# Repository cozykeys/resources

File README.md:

# CozyKeys Resources

- [./assets](./assets): Various assets used on CozyKeys website, keyboards, etc.
- [./concepts](./concepts): Unfinished keyboard concepts
- [./cozy-components](./cozy-components): Kicad symbol library
- [./cozy-parts.pretty](./cozy-parts.pretty): Kicad footprint library
- [./guides](./guides): Guides related to keyboard creation
- [./kbutil](./kbutil): .NET Core tools for accelerating keyboard creation
- [./scripts](./scripts): Various scripts related to keyboard creation

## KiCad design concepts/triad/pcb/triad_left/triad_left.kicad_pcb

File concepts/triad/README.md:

# CozyKeys Triad

TODO

## Using the Scripts

### Install Prerequisites

```bash
python3 -m pip install \
    mypy \
    sympy \
    openpyscad
```

### General Usage

```
./scripts/triad.py <command> <ARGUMENTS> [OPTIONS]
```

## Random Resources

- XML beautifier used to format layout files:
    - [XML Beautifier](https://xmlbeautifier.com)
- Script for scaling Kicad modules, useful for graphics:
    - [Kicad Module Scaler](http://www.smallbulb.net/kicad_mod-scaler)

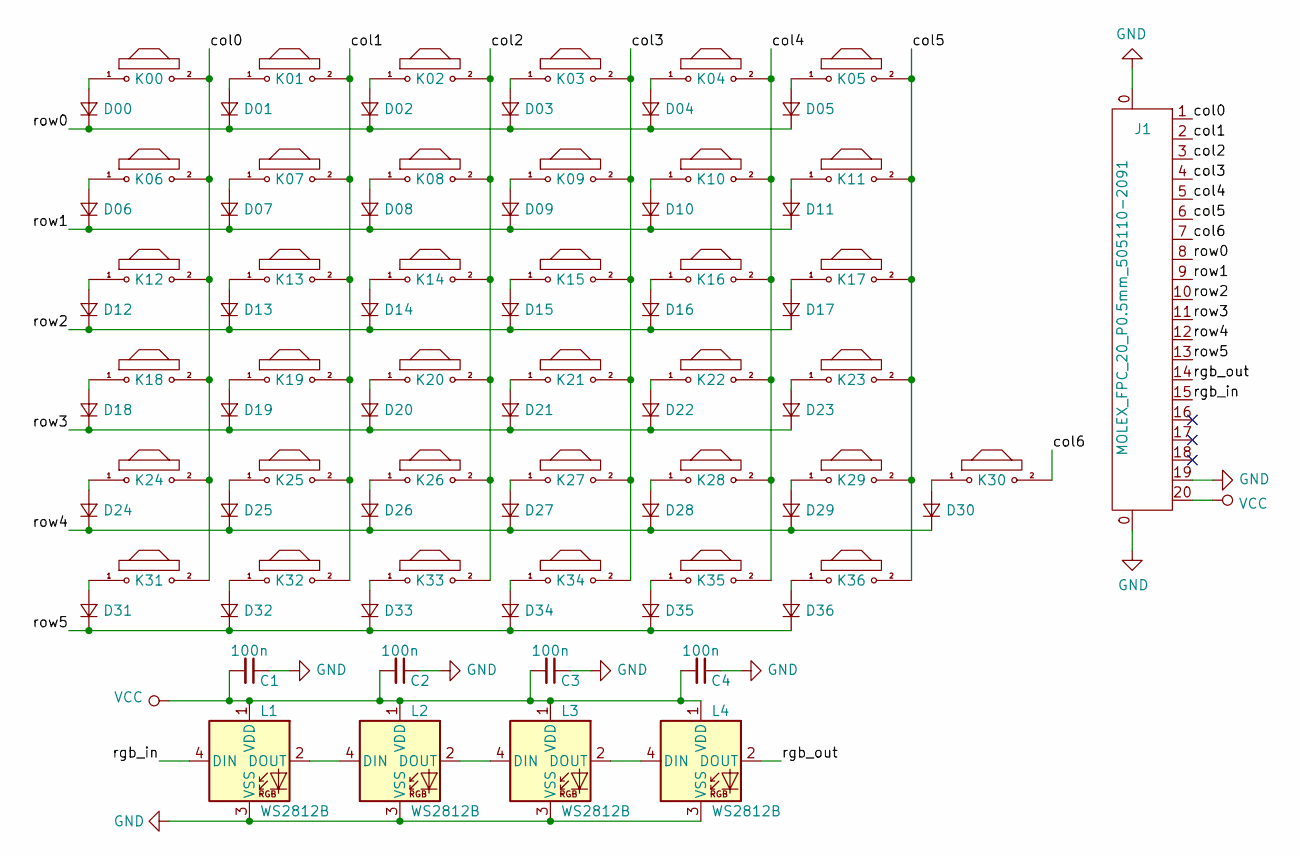
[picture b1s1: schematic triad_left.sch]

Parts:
C1, C2, C3, C4: 100n; C_0805_2012Metric_Pad1.15x1.40mm_HandSolder
D00, D01, D02, D03, D04, D05, D06, D07, D08, D09, D10, D11, D12, D13, D14, D15, D16, D17, D18, D19, D20, D21, D22, D23, D24, D25, D26, D27, D28, D29, D30, D31, D32, D33, D34, D35, D36: D_Small; D_SOD-123F
J1: MOLEX_FPC_20_P0.5mm_505110-2091
K00, K01, K02, K03, K04, K05, K06, K07, K08, K09, K10, K11, K12, K13, K14, K15, K16, K17, K18, K19, K20, K21, K22, K23, K24, K25, K26, K27, K28, K29, K30, K31, K32, K33, K34, K35, K36: MX; MX_1.00u
L1, L2, L3, L4: WS2812B; LED_WS2812B_PLCC4_5.0x5.0mm_P3.2mm

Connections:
/col0: J1.1, K00.2, K06.2, K12.2, K18.2, K24.2, K31.2
/col1: J1.2, K01.2, K07.2, K13.2, K19.2, K25.2, K32.2
/col2: J1.3, K02.2, K08.2, K14.2, K20.2, K26.2, K33.2
/col3: J1.4, K03.2, K09.2, K15.2, K21.2, K27.2, K34.2
/col4: J1.5, K04.2, K10.2, K16.2, K22.2, K28.2, K35.2
/col5: J1.6, K05.2, K11.2, K17.2, K23.2, K29.2, K36.2
/col6: J1.7, K30.2
/rgb_in: J1.15, L1.4 (DIN)
/rgb_out: J1.14, L4.2 (DOUT)
/row0: D00.1 (K), D01.1 (K), D02.1 (K), D03.1 (K), D04.1 (K), D05.1 (K), J1.8
/row1: D06.1 (K), D07.1 (K), D08.1 (K), D09.1 (K), D10.1 (K), D11.1 (K), J1.9
/row2: D12.1 (K), D13.1 (K), D14.1 (K), D15.1 (K), D16.1 (K), D17.1 (K), J1.10
/row3: D18.1 (K), D19.1 (K), D20.1 (K), D21.1 (K), D22.1 (K), D23.1 (K), J1.11
/row4: D24.1 (K), D25.1 (K), D26.1 (K), D27.1 (K), D28.1 (K), D29.1 (K), D30.1 (K), J1.12
/row5: D31.1 (K), D32.1 (K), D33.1 (K), D34.1 (K), D35.1 (K), D36.1 (K), J1.13
GND: C1.1, C2.1, C3.1, C4.1, J1.0, J1.19, L1.3 (VSS), L2.3 (VSS), L3.3 (VSS), L4.3 (VSS)
unnamed: D00.2 (A), K00.1
unnamed: D01.2 (A), K01.1
unnamed: D02.2 (A), K02.1
unnamed: D03.2 (A), K03.1
unnamed: D04.2 (A), K04.1
unnamed: D05.2 (A), K05.1
unnamed: D06.2 (A), K06.1
unnamed: D07.2 (A), K07.1
unnamed: D08.2 (A), K08.1
unnamed: D09.2 (A), K09.1
unnamed: D10.2 (A), K10.1
unnamed: D11.2 (A), K11.1
unnamed: D12.2 (A), K12.1
unnamed: D13.2 (A), K13.1
unnamed: D14.2 (A), K14.1
unnamed: D15.2 (A), K15.1
unnamed: D16.2 (A), K16.1
unnamed: D17.2 (A), K17.1
unnamed: D18.2 (A), K18.1
unnamed: D19.2 (A), K19.1
unnamed: D20.2 (A), K20.1
unnamed: D21.2 (A), K21.1
unnamed: D22.2 (A), K22.1
unnamed: D23.2 (A), K23.1
unnamed: D24.2 (A), K24.1
unnamed: D25.2 (A), K25.1
unnamed: D26.2 (A), K26.1
unnamed: D27.2 (A), K27.1
unnamed: D28.2 (A), K28.1
unnamed: D29.2 (A), K29.1
unnamed: D30.2 (A), K30.1
unnamed: D31.2 (A), K31.1
unnamed: D32.2 (A), K32.1
unnamed: D33.2 (A), K33.1
unnamed: D34.2 (A), K34.1
unnamed: D35.2 (A), K35.1
unnamed: D36.2 (A), K36.1
unnamed: L1.2 (DOUT), L2.4 (DIN)
unnamed: L2.2 (DOUT), L3.4 (DIN)
unnamed: L3.2 (DOUT), L4.4 (DIN)
VCC: C1.2, C2.2, C3.2, C4.2, J1.20, L1.1 (VDD), L2.1 (VDD), L3.1 (VDD), L4.1 (VDD)

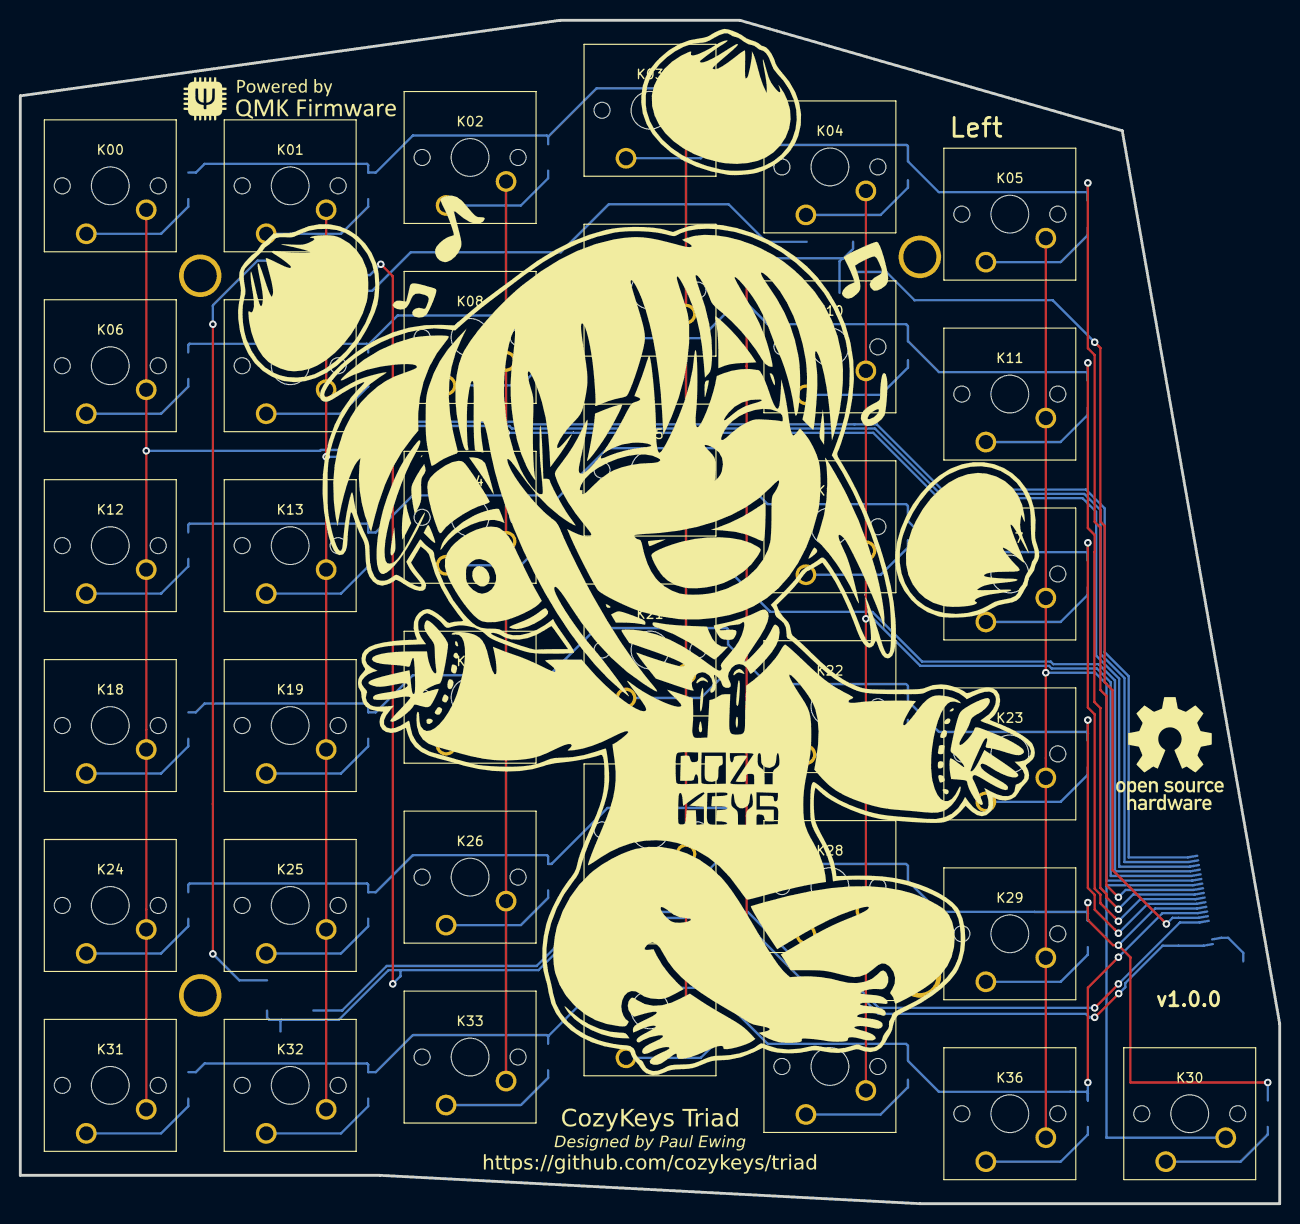
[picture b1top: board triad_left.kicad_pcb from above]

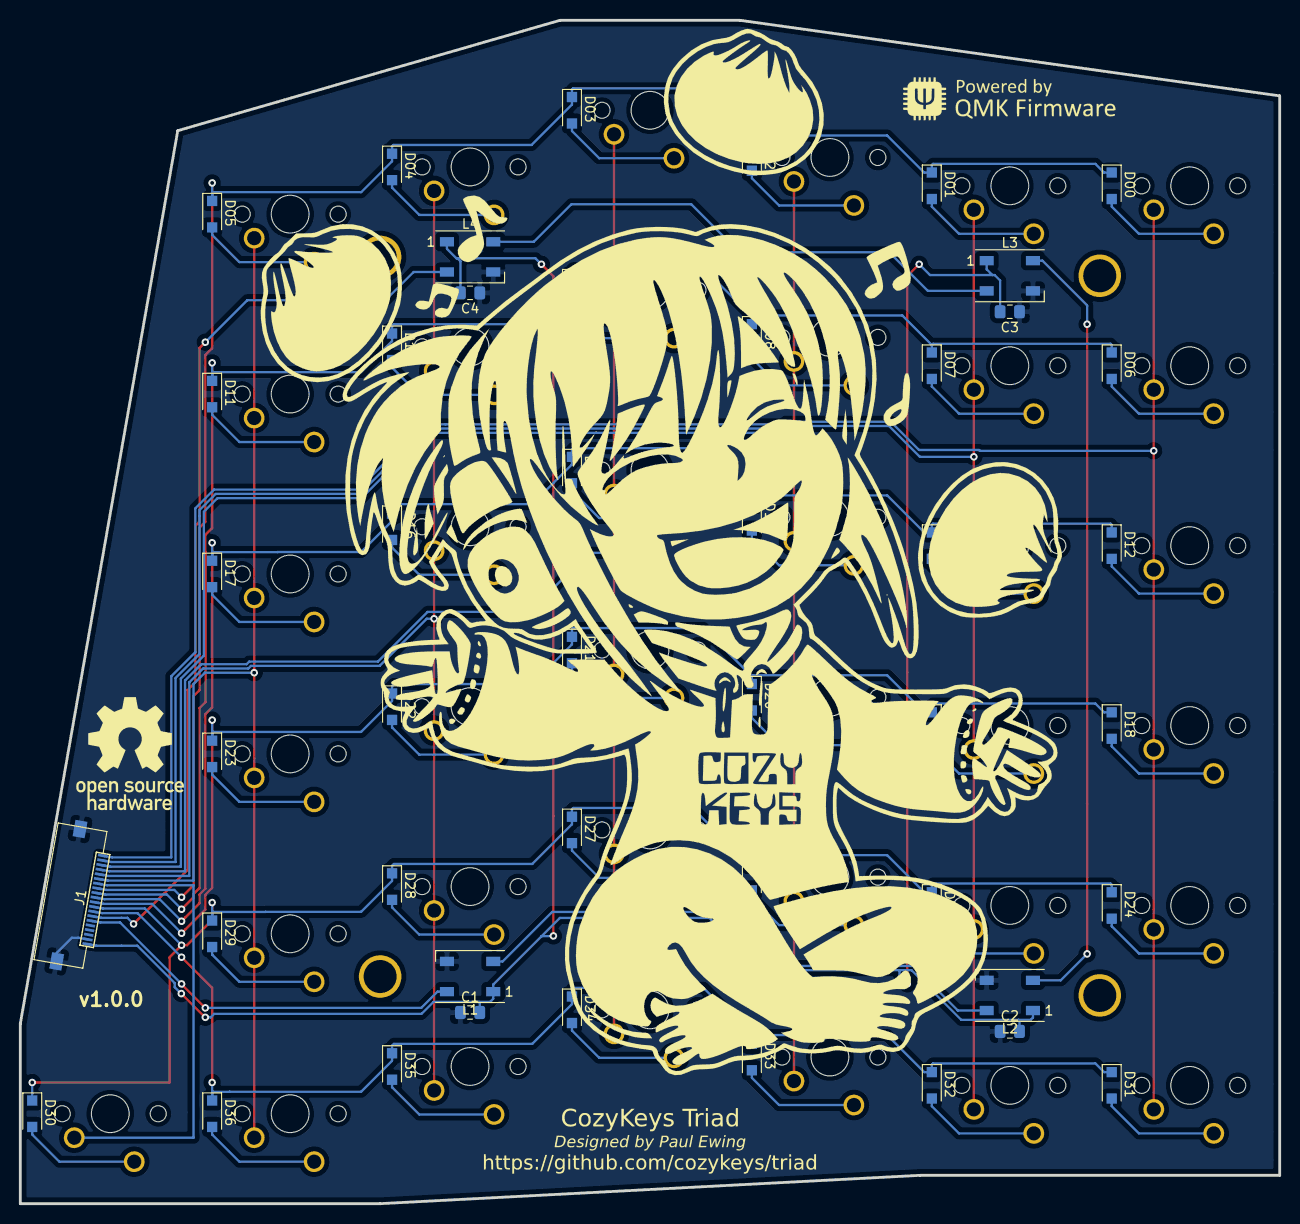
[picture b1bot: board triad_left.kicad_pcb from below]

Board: 2 copper layers, 133.3 x 125.3 mm, 93 parts (46 on the bottom side), 57 nets.

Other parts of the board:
G1, G2: LOGO; oshw-logo-small
G3, G4: qmk-badge
G5, G6: LOGO; triad-attribution-small
H1, H2, H3, H4: VAL**; HOLE_M2_SPACER

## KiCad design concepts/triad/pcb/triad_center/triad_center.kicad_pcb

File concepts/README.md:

# CozyKeys Concepts

This directory contains various concepts and unfinished keyboard designs.

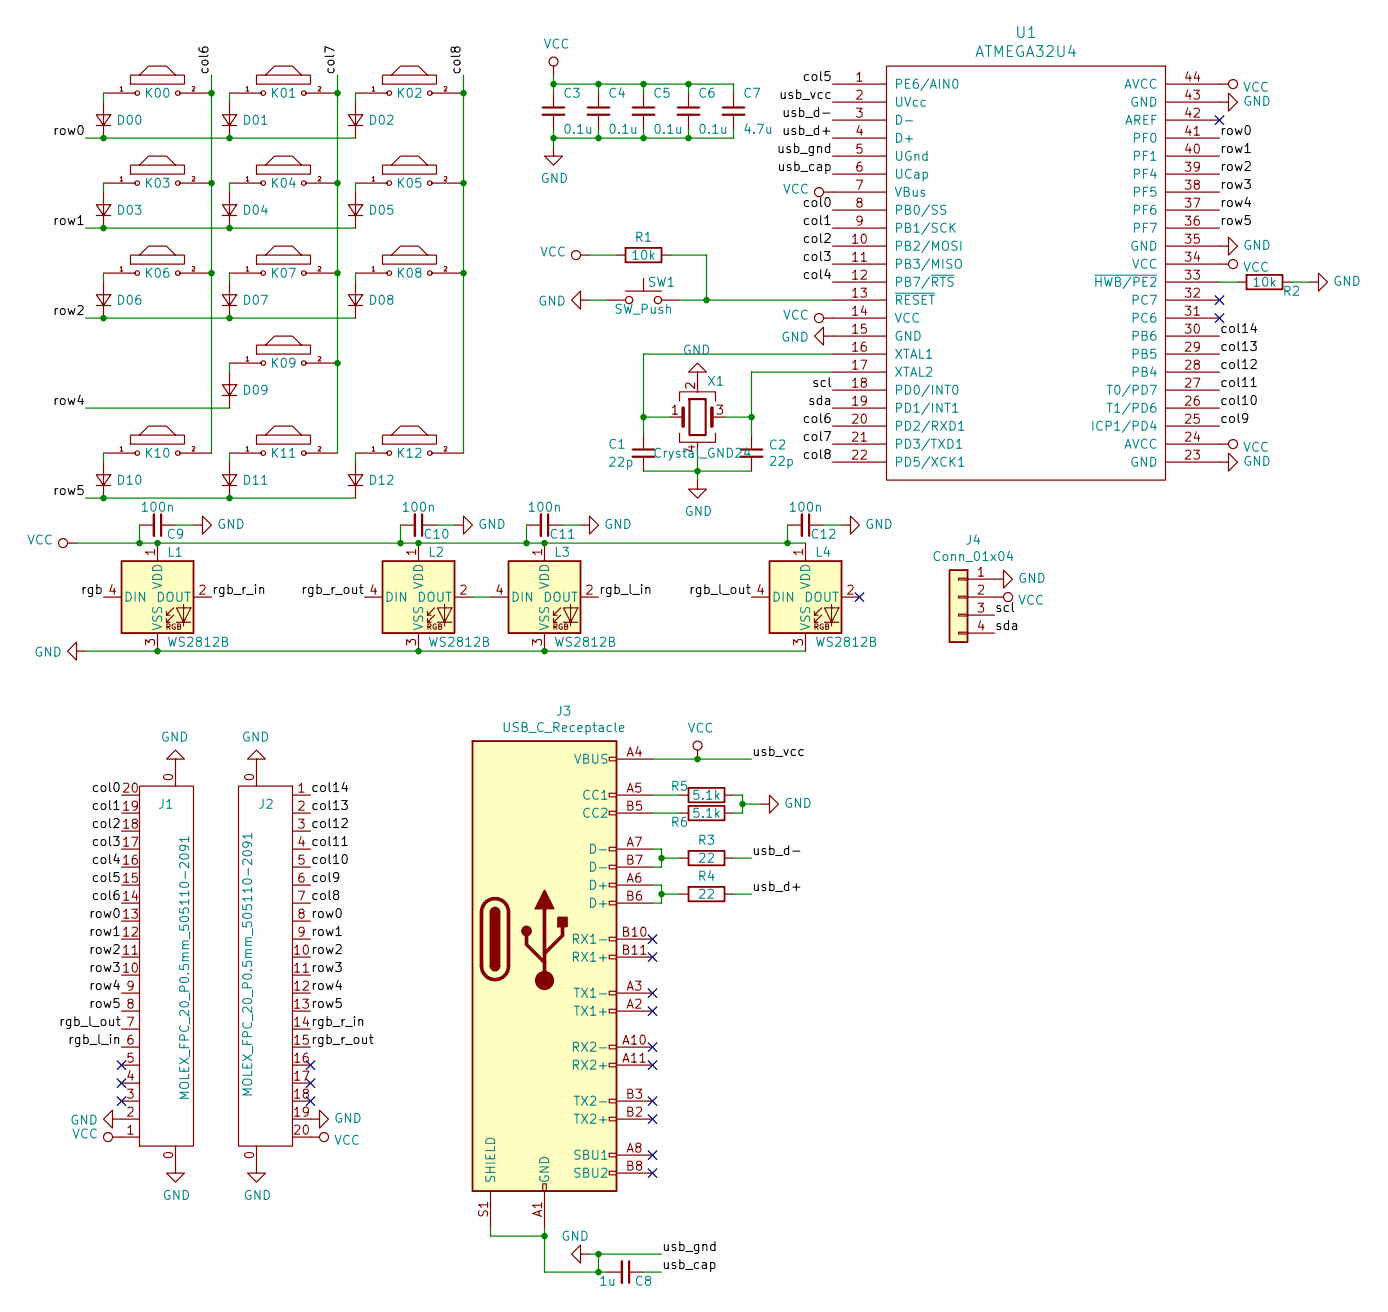
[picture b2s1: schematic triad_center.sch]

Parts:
C1, C2: 22p; C_0805_2012Metric_Pad1.15x1.40mm_HandSolder
C3, C4, C5, C6: 0.1u; C_0805_2012Metric_Pad1.15x1.40mm_HandSolder
C7: 4.7u; C_0805_2012Metric_Pad1.15x1.40mm_HandSolder
C8: 1u; C_0805_2012Metric_Pad1.15x1.40mm_HandSolder
C9, C10, C11, C12: 100n; C_0805_2012Metric_Pad1.15x1.40mm_HandSolder
D00, D01, D02, D03, D04, D05, D06, D07, D08, D09, D10, D11, D12: D_Small; D_SOD-123F
J1, J2: MOLEX_FPC_20_P0.5mm_505110-2091
J3: USB_C_Receptacle; USB_C_Receptacle_HRO_TYPE-C-31-M-12
J4: Conn_01x04; hiletgo_128x32_oled
K00, K01, K02, K03, K04, K05, K06, K07, K08, K09, K10, K11, K12: MX; MX_1.00u
L1, L2, L3, L4: WS2812B; LED_WS2812B_PLCC4_5.0x5.0mm_P3.2mm
R1, R2: 10k; R_0805_2012Metric_Pad1.15x1.40mm_HandSolder
R3, R4: 22; R_0805_2012Metric_Pad1.15x1.40mm_HandSolder
R5, R6: 5.1k; R_0805_2012Metric_Pad1.15x1.40mm_HandSolder
SW1: SW_Push; SW_TH_Tactile_Omron_B3F-10xx
U1: ATMEGA32U4; ATMEGA32U4-AU
X1: Crystal_GND24; Crystal_SMD_SeikoEpson_FA238-4Pin_3.2x2.5mm_HandSoldering

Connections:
/col0: J1.20, U1.8 (PB0/SS)
/col1: J1.19, U1.9 (PB1/SCK)
/col2: J1.18, U1.10 (PB2/MOSI)
/col3: J1.17, U1.11 (PB3/MISO)
/col4: J1.16, U1.12 (PB7/~RTS)
/col5: J1.15, U1.1 (PE6/AIN0)
/col6: J1.14, K00.2, K03.2, K06.2, K10.2, U1.20 (PD2/RXD1)
/col7: K01.2, K04.2, K07.2, K09.2, K11.2, U1.21 (PD3/TXD1)
/col8: J2.7, K02.2, K05.2, K08.2, K12.2, U1.22 (PD5/XCK1)
/col9: J2.6, U1.25 (ICP1/PD4)
/col10: J2.5, U1.26 (T1/PD6)
/col11: J2.4, U1.27 (T0/PD7)
/col12: J2.3, U1.28 (PB4)
/col13: J2.2, U1.29 (PB5)
/col14: J2.1, U1.30 (PB6)
/rgb: L1.4 (DIN)
/rgb_l_in: J1.6, L3.2 (DOUT)
/rgb_l_out: J1.7, L4.4 (DIN)
/rgb_r_in: J2.14, L1.2 (DOUT)
/rgb_r_out: J2.15, L2.4 (DIN)
/row0: D00.1 (K), D01.1 (K), D02.1 (K), J1.13, J2.8, U1.41 (PF0)
/row1: D03.1 (K), D04.1 (K), D05.1 (K), J1.12, J2.9, U1.40 (PF1)
/row2: D06.1 (K), D07.1 (K), D08.1 (K), J1.11, J2.10, U1.39 (PF4)
/row3: J1.10, J2.11, U1.38 (PF5)
/row4: D09.1 (K), J1.9, J2.12, U1.37 (PF6)
/row5: D10.1 (K), D11.1 (K), D12.1 (K), J1.8, J2.13, U1.36 (PF7)
/scl: J4.3, U1.18 (PD0/INT0)
/sda: J4.4, U1.19 (PD1/INT1)
/usb_cap: C8.1, U1.6 (UCap)
/usb_d+: R4.1, U1.4 (D+)
/usb_d-: R3.1, U1.3 (D-)
GND: C1.2, C2.2, C3.2, C4.2, C5.2, C6.2, C7.2, C8.2, C9.1, C10.1, C11.1, C12.1, J1.0, J1.2, J2.0, J2.19, J3.A1 (GND), J3.A12 (GND), J3.B1 (GND), J3.B12 (GND), J3.S1 (SHIELD), J4.1, L1.3 (VSS), L2.3 (VSS), L3.3 (VSS), L4.3 (VSS), R2.1, R5.1, R6.1, SW1.1, U1.5 (UGnd), U1.15 (GND), U1.23 (GND), U1.35 (GND), U1.43 (GND), X1.2, X1.4
unnamed: C1.1, U1.16 (XTAL1), X1.1
unnamed: C2.1, U1.17 (XTAL2), X1.3
unnamed: D00.2 (A), K00.1
unnamed: D01.2 (A), K01.1
unnamed: D02.2 (A), K02.1
unnamed: D03.2 (A), K03.1
unnamed: D04.2 (A), K04.1
unnamed: D05.2 (A), K05.1
unnamed: D06.2 (A), K06.1
unnamed: D07.2 (A), K07.1
unnamed: D08.2 (A), K08.1
unnamed: D09.2 (A), K09.1
unnamed: D10.2 (A), K10.1
unnamed: D11.2 (A), K11.1
unnamed: D12.2 (A), K12.1
unnamed: J3.A5 (CC1), R5.2
unnamed: J3.A6 (D+), J3.B6 (D+), R4.2
unnamed: J3.A7 (D-), J3.B7 (D-), R3.2
unnamed: J3.B5 (CC2), R6.2
unnamed: L2.2 (DOUT), L3.4 (DIN)
unnamed: R1.1, SW1.2, U1.13 (~RESET)
unnamed: R2.2, U1.33 (~HWB/PE2)
VCC: C3.1, C4.1, C5.1, C6.1, C7.1, C9.2, C10.2, C11.2, C12.2, J1.1, J2.20, J3.A4 (VBUS), J3.A9 (VBUS), J3.B4 (VBUS), J3.B9 (VBUS), J4.2, L1.1 (VDD), L2.1 (VDD), L3.1 (VDD), L4.1 (VDD), R1.2, U1.2 (UVcc), U1.7 (VBus), U1.14 (VCC), U1.24 (AVCC), U1.34 (VCC), U1.44 (AVCC)

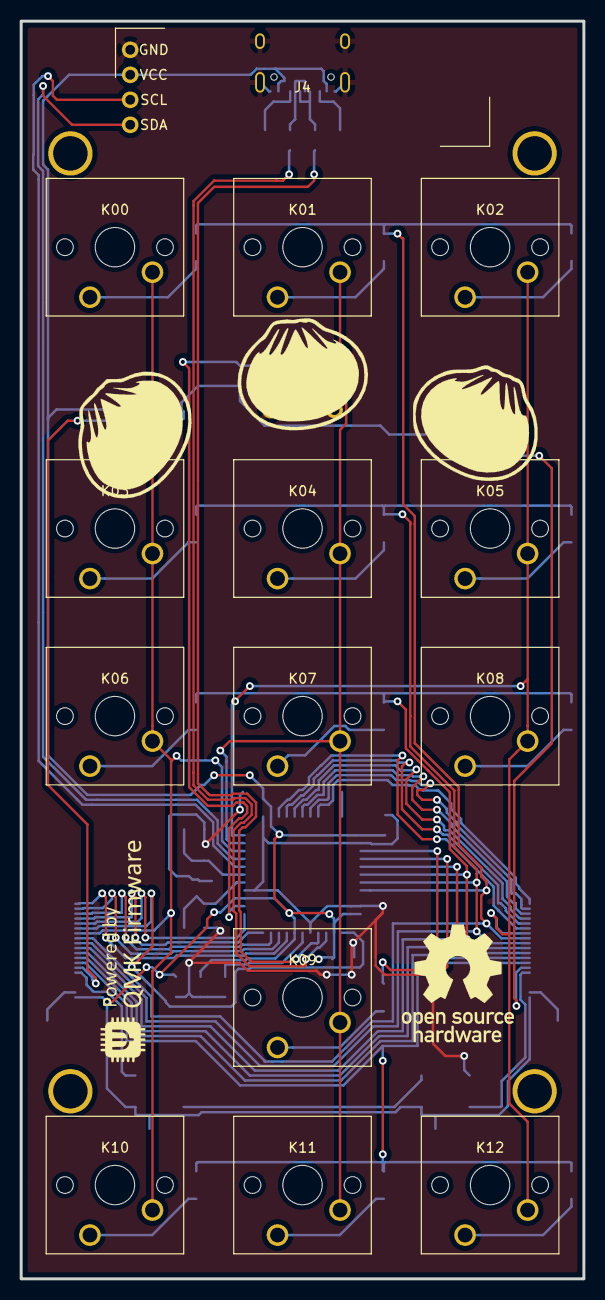
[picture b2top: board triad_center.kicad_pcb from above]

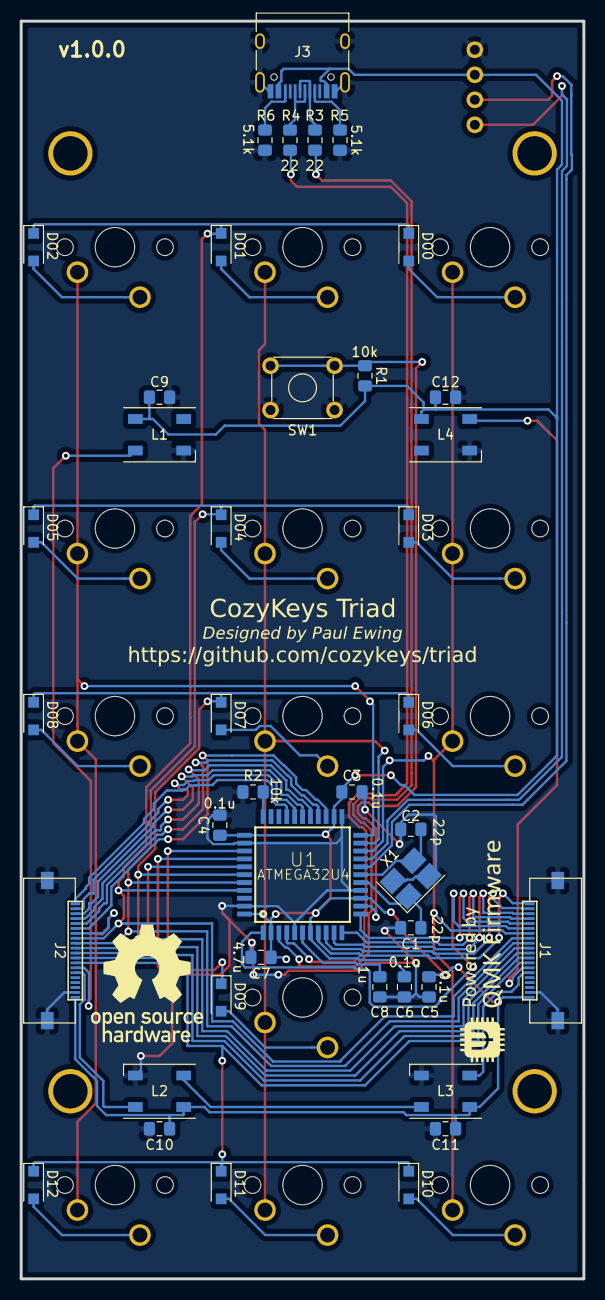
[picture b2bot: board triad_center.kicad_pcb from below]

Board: 2 copper layers, 57.1 x 127.7 mm, 59 parts (41 on the bottom side), 54 nets.

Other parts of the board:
H1, H2, H3, H4: VAL**; HOLE_M2_SPACER

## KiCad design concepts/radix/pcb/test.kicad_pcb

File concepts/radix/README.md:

# CozyKeys Radix

This repository contains the design files for the CozyKeys Radix keyboard. This
keyboard is still early in the design phase and is a work in progress.

## TODO List
- [ ] Add in-switch LEDs
    - [ ] Reverse engineer how the Iris supports these
    - [ ] Update the PCB (And generation tools/scripts)
    - [ ] Find a suitable SMD LED part number

## Resources

### Keyboard PCB Design Tutorial

https://github.com/ruiqimao/keyboard-pcb-guide

### OLED Diplays

Adafruit has two different 128x32 OLED display modules but I believe the I2C
one is preferable. Other keyboards that have integrated SSD1306 displays have
used I2C display modules.

```
- 0.91" 128x32 Adafruit Display Modules
    - I2C
        - Schematic: https://github.com/adafruit/Adafruit-128x32-I2C-OLED-Breakout-PCB
        - Product Page: https://www.adafruit.com/product/931
        - Underlying Display Component: UG-2832HSWEG02
            - Datasheet: https://cdn-shop.adafruit.com/datasheets/UG-2832HSWEG02.pdf
    - SPI
        - Schematic: https://github.com/adafruit/Adafruit-128x32-SPI-OLED-breakout-board-PCB
        - Product Page: https://www.adafruit.com/product/661
        - Underlying Display Module: UG-2832HSWEG04
            - Datasheet: https://cdn-shop.adafruit.com/datasheets/UG-2832HSWEG04.pdf
```

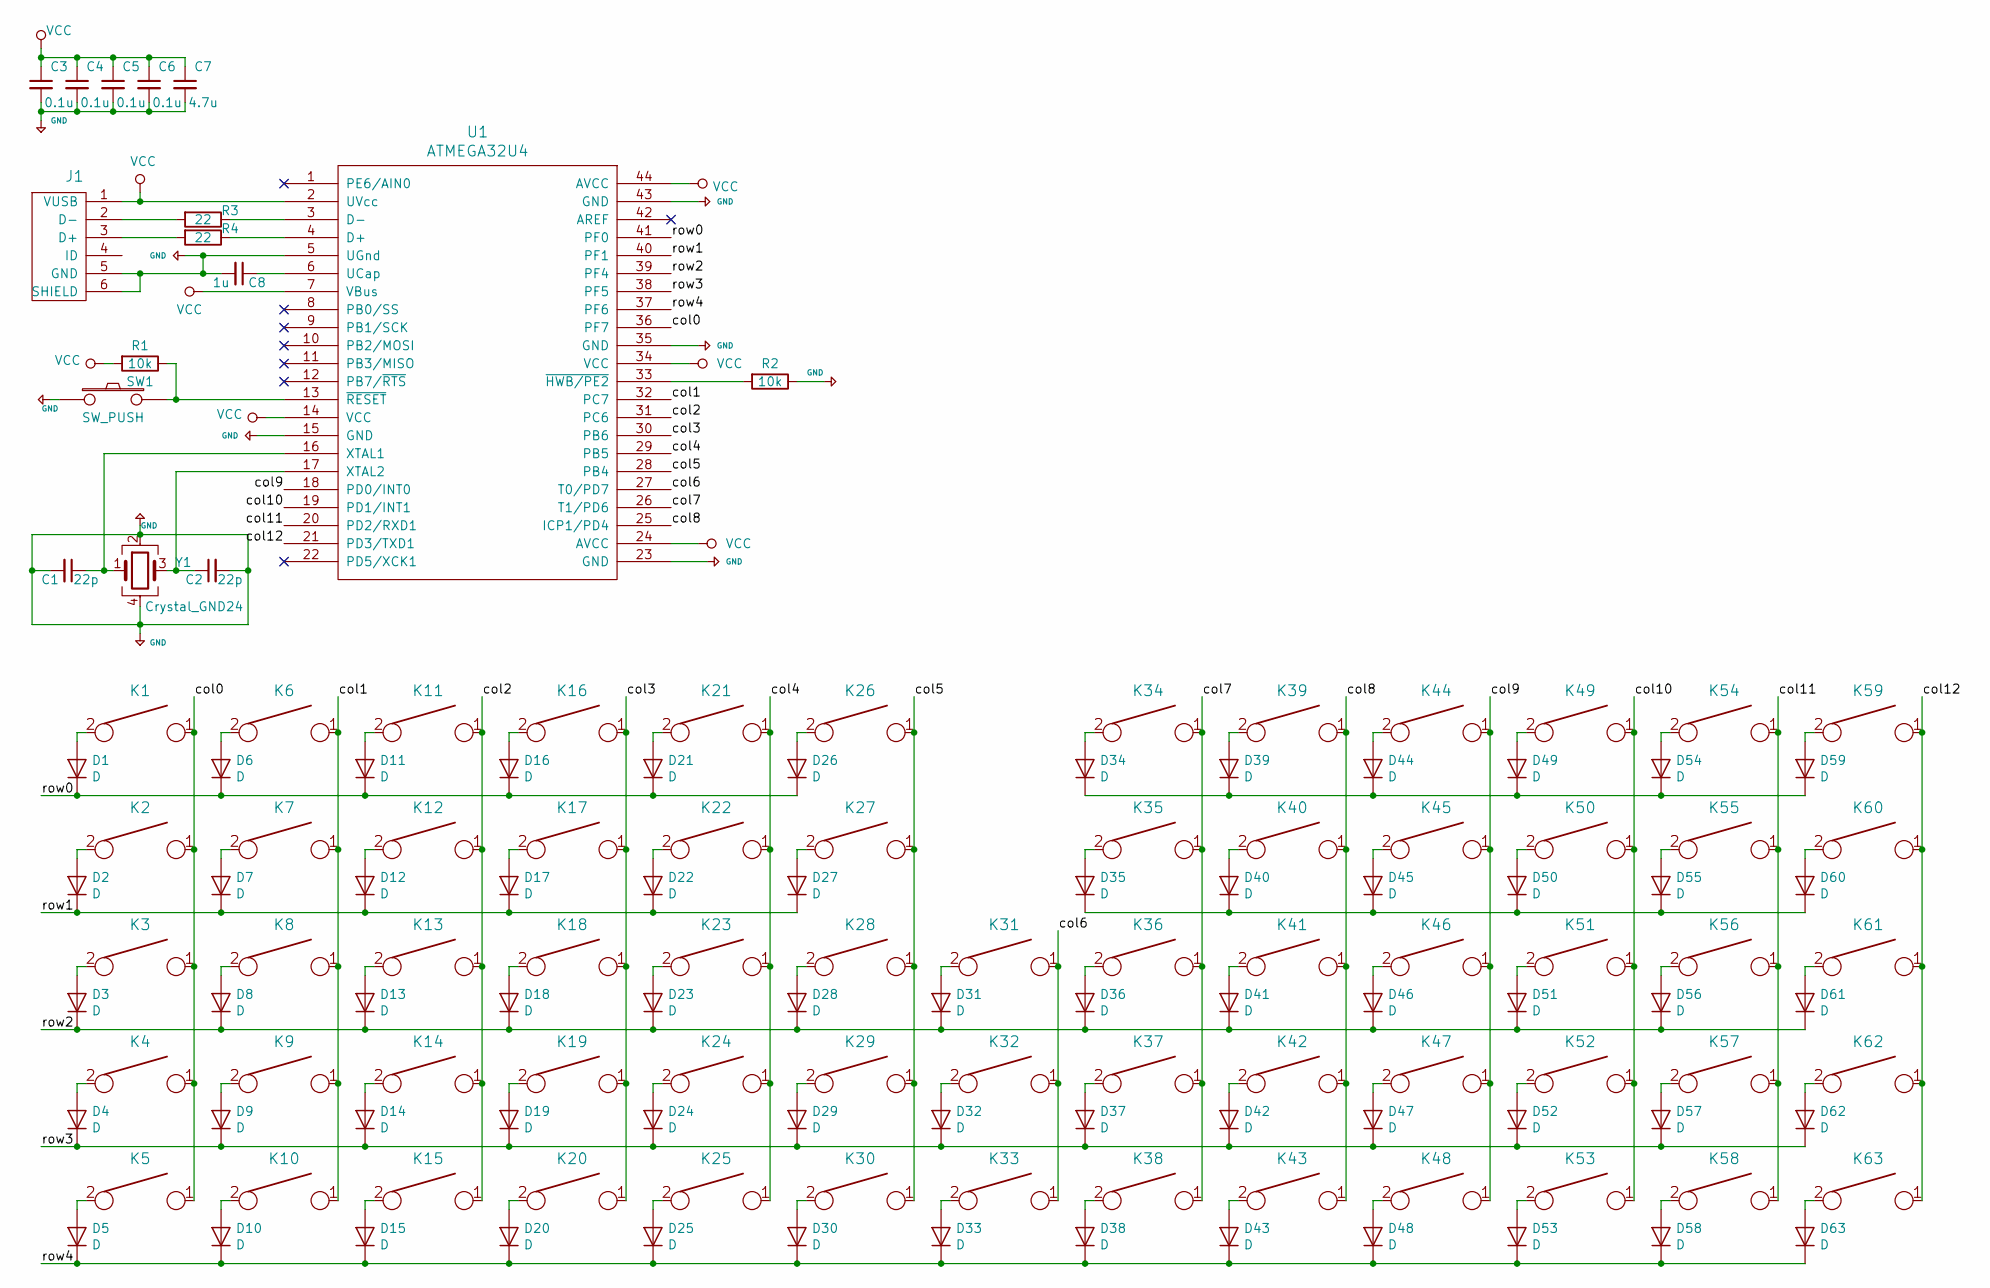
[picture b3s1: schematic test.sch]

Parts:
C1, C2: 22p; C_0805_2012Metric_Pad1.15x1.40mm_HandSolder
C3, C4, C5, C6: 0.1u; C_0805_2012Metric_Pad1.15x1.40mm_HandSolder
C7: 4.7u; C_0805_2012Metric_Pad1.15x1.40mm_HandSolder
C8: 1u; C_0805_2012Metric_Pad1.15x1.40mm_HandSolder
D1, D2, D3, D4, D5, D6, D7, D8, D9, D10, D11, D12, D13, D14, D15, D16, D17, D18, D19, D20, D21, D22, D23, D24, D25, D26, D27, D28, D29, D30, D31, D32, D33, D34, D35, D36, D37, D38, D39, D40, D41, D42, D43, D44, D45, D46, D47, D48, D49, D50, D51, D52, D53, D54, D55, D56, D57, D58, D59, D60, D61, D62, D63: D; D_SOD123_axial
J1: USB_mini_micro_B; USB_microB
K1, K2, K3, K4, K5, K6, K7, K8, K9, K10, K11, K12, K13, K14, K15, K16, K17, K18, K19, K20, K21, K22, K23, K24, K25, K26, K27, K28, K29, K30, K31, K32, K33, K34, K35, K36, K37, K38, K39, K40, K41, K42, K43, K44, K45, K46, K47, K48, K49, K50, K51, K52, K53, K54, K55, K56, K57, K58, K59, K60, K61, K62, K63: KEYSW; Mx_Alps_100
R1, R2: 10k; R_0805_2012Metric_Pad1.15x1.40mm_HandSolder
R3, R4: 22; R_0805_2012Metric_Pad1.15x1.40mm_HandSolder
SW1: SW_PUSH; SW_SPST_TL3342
U1: ATMEGA32U4; TQFP-44_10x10mm_P0.8mm
Y1: Crystal_GND24; Crystal_SMD_SeikoEpson_FA238-4Pin_3.2x2.5mm_HandSoldering

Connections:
+5V: C1.2, C2.2, C3.2, C4.2, C5.2, C6.2, C7.2, C8.2, J1.5 (GND), J1.6 (SHIELD), R2.1, SW1.1, U1.5 (UGnd), U1.15 (GND), U1.23 (GND), U1.35 (GND), U1.43 (GND), Y1.2, Y1.4
/col0: K1.1, K2.1, K3.1, K4.1, K5.1, U1.36 (PF7)
/col1: K6.1, K7.1, K8.1, K9.1, K10.1, U1.32 (PC7)
/col2: K11.1, K12.1, K13.1, K14.1, K15.1, U1.31 (PC6)
/col3: K16.1, K17.1, K18.1, K19.1, K20.1, U1.30 (PB6)
/col4: K21.1, K22.1, K23.1, K24.1, K25.1, U1.29 (PB5)
/col5: K26.1, K27.1, K28.1, K29.1, K30.1, U1.28 (PB4)
/col6: K31.1, K32.1, K33.1, U1.27 (T0/PD7)
/col7: K34.1, K35.1, K36.1, K37.1, K38.1, U1.26 (T1/PD6)
/col8: K39.1, K40.1, K41.1, K42.1, K43.1, U1.25 (ICP1/PD4)
/col9: K44.1, K45.1, K46.1, K47.1, K48.1, U1.18 (PD0/INT0)
/col10: K49.1, K50.1, K51.1, K52.1, K53.1, U1.19 (PD1/INT1)
/col11: K54.1, K55.1, K56.1, K57.1, K58.1, U1.20 (PD2/RXD1)
/col12: K59.1, K60.1, K61.1, K62.1, K63.1, U1.21 (PD3/TXD1)
/row0: D1.1 (K), D6.1 (K), D11.1 (K), D16.1 (K), D21.1 (K), D26.1 (K), U1.41 (PF0)
/row1: D2.1 (K), D7.1 (K), D12.1 (K), D17.1 (K), D22.1 (K), D27.1 (K), U1.40 (PF1)
/row2: D3.1 (K), D8.1 (K), D13.1 (K), D18.1 (K), D23.1 (K), D28.1 (K), D31.1 (K), D36.1 (K), D41.1 (K), D46.1 (K), D51.1 (K), D56.1 (K), D61.1 (K), U1.39 (PF4)
/row3: D4.1 (K), D9.1 (K), D14.1 (K), D19.1 (K), D24.1 (K), D29.1 (K), D32.1 (K), D37.1 (K), D42.1 (K), D47.1 (K), D52.1 (K), D57.1 (K), D62.1 (K), U1.38 (PF5)
/row4: D5.1 (K), D10.1 (K), D15.1 (K), D20.1 (K), D25.1 (K), D30.1 (K), D33.1 (K), D38.1 (K), D43.1 (K), D48.1 (K), D53.1 (K), D58.1 (K), D63.1 (K), U1.37 (PF6)
unnamed: C1.1, U1.16 (XTAL1), Y1.1
unnamed: C2.1, U1.17 (XTAL2), Y1.3
unnamed: C8.1, U1.6 (UCap)
unnamed: D1.2 (A), K1.2
unnamed: D2.2 (A), K2.2
unnamed: D3.2 (A), K3.2
unnamed: D4.2 (A), K4.2
unnamed: D5.2 (A), K5.2
unnamed: D6.2 (A), K6.2
unnamed: D7.2 (A), K7.2
unnamed: D8.2 (A), K8.2
unnamed: D9.2 (A), K9.2
unnamed: D10.2 (A), K10.2
unnamed: D11.2 (A), K11.2
unnamed: D12.2 (A), K12.2
unnamed: D13.2 (A), K13.2
unnamed: D14.2 (A), K14.2
unnamed: D15.2 (A), K15.2
unnamed: D16.2 (A), K16.2
unnamed: D17.2 (A), K17.2
unnamed: D18.2 (A), K18.2
unnamed: D19.2 (A), K19.2
unnamed: D20.2 (A), K20.2
unnamed: D21.2 (A), K21.2
unnamed: D22.2 (A), K22.2
unnamed: D23.2 (A), K23.2
unnamed: D24.2 (A), K24.2
unnamed: D25.2 (A), K25.2
unnamed: D26.2 (A), K26.2
unnamed: D27.2 (A), K27.2
unnamed: D28.2 (A), K28.2
unnamed: D29.2 (A), K29.2
unnamed: D30.2 (A), K30.2
unnamed: D31.2 (A), K31.2
unnamed: D32.2 (A), K32.2
unnamed: D33.2 (A), K33.2
unnamed: D34.1 (K), D39.1 (K), D44.1 (K), D49.1 (K), D54.1 (K), D59.1 (K)
unnamed: D34.2 (A), K34.2
unnamed: D35.1 (K), D40.1 (K), D45.1 (K), D50.1 (K), D55.1 (K), D60.1 (K)
unnamed: D35.2 (A), K35.2
unnamed: D36.2 (A), K36.2
unnamed: D37.2 (A), K37.2
unnamed: D38.2 (A), K38.2
unnamed: D39.2 (A), K39.2
unnamed: D40.2 (A), K40.2
unnamed: D41.2 (A), K41.2
unnamed: D42.2 (A), K42.2
unnamed: D43.2 (A), K43.2
unnamed: D44.2 (A), K44.2
unnamed: D45.2 (A), K45.2
unnamed: D46.2 (A), K46.2
unnamed: D47.2 (A), K47.2
unnamed: D48.2 (A), K48.2
unnamed: D49.2 (A), K49.2
unnamed: D50.2 (A), K50.2
unnamed: D51.2 (A), K51.2
unnamed: D52.2 (A), K52.2
unnamed: D53.2 (A), K53.2
unnamed: D54.2 (A), K54.2
unnamed: D55.2 (A), K55.2
unnamed: D56.2 (A), K56.2
unnamed: D57.2 (A), K57.2
unnamed: D58.2 (A), K58.2
unnamed: D59.2 (A), K59.2
unnamed: D60.2 (A), K60.2
unnamed: D61.2 (A), K61.2
unnamed: D62.2 (A), K62.2
unnamed: D63.2 (A), K63.2
unnamed: J1.2 (D-), R3.2
unnamed: J1.3 (D+), R4.2
unnamed: R1.1, SW1.2, U1.13 (~RESET)
unnamed: R2.2, U1.33 (~HWB/PE2)
unnamed: R3.1, U1.3 (D-)
unnamed: R4.1, U1.4 (D+)
VCC: C3.1, C4.1, C5.1, C6.1, C7.1, J1.1 (VUSB), R1.2, U1.2 (UVcc), U1.7 (VBus), U1.14 (VCC), U1.24 (AVCC), U1.34 (VCC), U1.44 (AVCC)

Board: 2 copper layers, 142 parts (0 on the bottom side), 94 nets, no tracks yet.

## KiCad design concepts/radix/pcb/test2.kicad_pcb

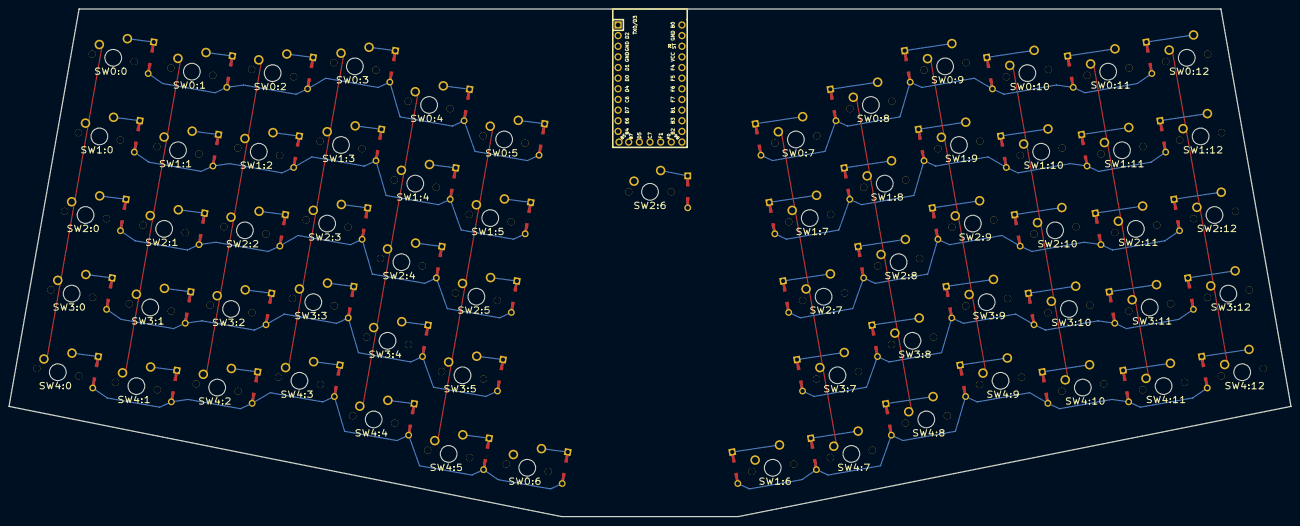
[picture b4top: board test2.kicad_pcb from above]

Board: 2 copper layers, 305.9 x 121.1 mm, 127 parts (0 on the bottom side), 81 nets.

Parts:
D0:0, D0:1, D0:2, D0:3, D0:4, D0:5, D0:6, D0:7, D0:8, D0:9, D0:10, D0:11, D0:12, D1:0, D1:1, D1:2, D1:3, D1:4, D1:5, D1:6, D1:7, D1:8, D1:9, D1:10, D1:11, D1:12, D2:0, D2:1, D2:2, D2:3, D2:4, D2:5, D2:6, D2:7, D2:8, D2:9, D2:10, D2:11, D2:12, D3:0, D3:1, D3:2, D3:3, D3:4, D3:5, D3:7, D3:8, D3:9, D3:10, D3:11, D3:12, D4:0, D4:1, D4:2, D4:3, D4:4, D4:5, D4:7, D4:8, D4:9, D4:10, D4:11, D4:12: DIODE
SW0:0, SW0:1, SW0:2, SW0:3, SW0:4, SW0:5, SW0:6, SW0:7, SW0:8, SW0:9, SW0:10, SW0:11, SW0:12, SW1:0, SW1:1, SW1:2, SW1:3, SW1:4, SW1:5, SW1:6, SW1:7, SW1:8, SW1:9, SW1:10, SW1:11, SW1:12, SW2:0, SW2:1, SW2:2, SW2:3, SW2:4, SW2:5, SW2:6, SW2:7, SW2:8, SW2:9, SW2:10, SW2:11, SW2:12, SW3:0, SW3:1, SW3:2, SW3:3, SW3:4, SW3:5, SW3:7, SW3:8, SW3:9, SW3:10, SW3:11, SW3:12, SW4:0, SW4:1, SW4:2, SW4:3, SW4:4, SW4:5, SW4:7, SW4:8, SW4:9, SW4:10, SW4:11, SW4:12: MX
U1: Elite-C

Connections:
N-col-0: SW0:0.2, SW1:0.2, SW2:0.2, SW3:0.2, SW4:0.2
N-col-1: SW0:1.2, SW1:1.2, SW2:1.2, SW3:1.2, SW4:1.2
N-col-2: SW0:2.2, SW1:2.2, SW2:2.2, SW3:2.2, SW4:2.2
N-col-3: SW0:3.2, SW1:3.2, SW2:3.2, SW3:3.2, SW4:3.2
N-col-4: SW0:4.2, SW1:4.2, SW2:4.2, SW3:4.2, SW4:4.2
N-col-5: SW0:5.2, SW1:5.2, SW2:5.2, SW3:5.2, SW4:5.2
N-col-6: SW0:6.2, SW1:6.2, SW2:6.2
N-col-7: SW0:7.2, SW1:7.2, SW2:7.2, SW3:7.2, SW4:7.2
N-col-8: SW0:8.2, SW1:8.2, SW2:8.2, SW3:8.2, SW4:8.2
N-col-9: SW0:9.2, SW1:9.2, SW2:9.2, SW3:9.2, SW4:9.2
N-col-10: SW0:10.2, SW1:10.2, SW2:10.2, SW3:10.2, SW4:10.2
N-col-11: SW0:11.2, SW1:11.2, SW2:11.2, SW3:11.2, SW4:11.2
N-col-12: SW0:12.2, SW1:12.2, SW2:12.2, SW3:12.2, SW4:12.2
N-diode-0-0: D0:0.2, SW0:0.1
N-diode-0-1: D0:1.2, SW0:1.1
N-diode-0-2: D0:2.2, SW0:2.1
N-diode-0-3: D0:3.2, SW0:3.1
N-diode-0-4: D0:4.2, SW0:4.1
N-diode-0-5: D0:5.2, SW0:5.1
N-diode-0-6: D0:6.2, SW0:6.1
N-diode-0-7: D0:7.2, SW0:7.1
N-diode-0-8: D0:8.2, SW0:8.1
N-diode-0-9: D0:9.2, SW0:9.1
N-diode-0-10: D0:10.2, SW0:10.1
N-diode-0-11: D0:11.2, SW0:11.1
N-diode-0-12: D0:12.2, SW0:12.1
N-diode-1-0: D1:0.2, SW1:0.1
N-diode-1-1: D1:1.2, SW1:1.1
N-diode-1-2: D1:2.2, SW1:2.1
N-diode-1-3: D1:3.2, SW1:3.1
N-diode-1-4: D1:4.2, SW1:4.1
N-diode-1-5: D1:5.2, SW1:5.1
N-diode-1-6: D1:6.2, SW1:6.1
N-diode-1-7: D1:7.2, SW1:7.1
N-diode-1-8: D1:8.2, SW1:8.1
N-diode-1-9: D1:9.2, SW1:9.1
N-diode-1-10: D1:10.2, SW1:10.1
N-diode-1-11: D1:11.2, SW1:11.1
N-diode-1-12: D1:12.2, SW1:12.1
N-diode-2-0: D2:0.2, SW2:0.1
N-diode-2-1: D2:1.2, SW2:1.1
N-diode-2-2: D2:2.2, SW2:2.1
N-diode-2-3: D2:3.2, SW2:3.1
N-diode-2-4: D2:4.2, SW2:4.1
N-diode-2-5: D2:5.2, SW2:5.1
N-diode-2-6: D2:6.2, SW2:6.1
N-diode-2-7: D2:7.2, SW2:7.1
N-diode-2-8: D2:8.2, SW2:8.1
N-diode-2-9: D2:9.2, SW2:9.1
N-diode-2-10: D2:10.2, SW2:10.1
N-diode-2-11: D2:11.2, SW2:11.1
N-diode-2-12: D2:12.2, SW2:12.1
N-diode-3-0: D3:0.2, SW3:0.1
N-diode-3-1: D3:1.2, SW3:1.1
N-diode-3-2: D3:2.2, SW3:2.1
N-diode-3-3: D3:3.2, SW3:3.1
N-diode-3-4: D3:4.2, SW3:4.1
N-diode-3-5: D3:5.2, SW3:5.1
N-diode-3-7: D3:7.2, SW3:7.1
N-diode-3-8: D3:8.2, SW3:8.1
N-diode-3-9: D3:9.2, SW3:9.1
N-diode-3-10: D3:10.2, SW3:10.1
N-diode-3-11: D3:11.2, SW3:11.1
N-diode-3-12: D3:12.2, SW3:12.1
N-diode-4-0: D4:0.2, SW4:0.1
N-diode-4-1: D4:1.2, SW4:1.1
N-diode-4-2: D4:2.2, SW4:2.1
N-diode-4-3: D4:3.2, SW4:3.1
N-diode-4-4: D4:4.2, SW4:4.1
N-diode-4-5: D4:5.2, SW4:5.1
N-diode-4-7: D4:7.2, SW4:7.1
N-diode-4-8: D4:8.2, SW4:8.1
N-diode-4-9: D4:9.2, SW4:9.1
N-diode-4-10: D4:10.2, SW4:10.1
N-diode-4-11: D4:11.2, SW4:11.1
N-diode-4-12: D4:12.2, SW4:12.1
N-row-0: D0:0.1, D0:1.1, D0:2.1, D0:3.1, D0:4.1, D0:5.1, D0:6.1, D0:7.1, D0:8.1, D0:9.1, D0:10.1, D0:11.1, D0:12.1
N-row-1: D1:0.1, D1:1.1, D1:2.1, D1:3.1, D1:4.1, D1:5.1, D1:6.1, D1:7.1, D1:8.1, D1:9.1, D1:10.1, D1:11.1, D1:12.1
N-row-2: D2:0.1, D2:1.1, D2:2.1, D2:3.1, D2:4.1, D2:5.1, D2:6.1, D2:7.1, D2:8.1, D2:9.1, D2:10.1, D2:11.1, D2:12.1
N-row-3: D3:0.1, D3:1.1, D3:2.1, D3:3.1, D3:4.1, D3:5.1, D3:7.1, D3:8.1, D3:9.1, D3:10.1, D3:11.1, D3:12.1
N-row-4: D4:0.1, D4:1.1, D4:2.1, D4:3.1, D4:4.1, D4:5.1, D4:7.1, D4:8.1, D4:9.1, D4:10.1, D4:11.1, D4:12.1
